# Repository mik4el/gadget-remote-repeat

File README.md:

# Remote repeat
Repeats IR remote signals received at e.g. a TV to a connected IR LED connected to a long wire placed e.g. inside a cabinet. This is also a minimal footprint platform to receive standard IR signals, manipulate them and to send standard IR signals.

## Hardware
The hardware consists of a standard IR receiver (TSOP38238) and an Attiny85 to process the signal and to control sending a new signal. The application is powered by USB micro from e.g. the USB output from a TV.

The pcb, where more details can be found in the hardware folder, is a minimal two layer pcb for the application. The top view of the current pcb can be viewed below:

## Software dependencies
The software is based on Arduino and uses the external library tiny_IRremote adopted by https://github.com/SeeJayDee from the popular https://github.com/z3t0/Arduino-IRremote library. I have made modifications to the library to be even smaller for the current usage. The modified library is in ```gadget-remote-repeat-tiny```. To include the current library please follow e.g. https://www.arduino.cc/en/Guide/Libraries to install an external library.

## Structure of repo
For an Attiny85 version of the software, please see ```gadget-remote-repeat-tiny```. For other Arduino platforms please see ```gadget-remote-repeat```.

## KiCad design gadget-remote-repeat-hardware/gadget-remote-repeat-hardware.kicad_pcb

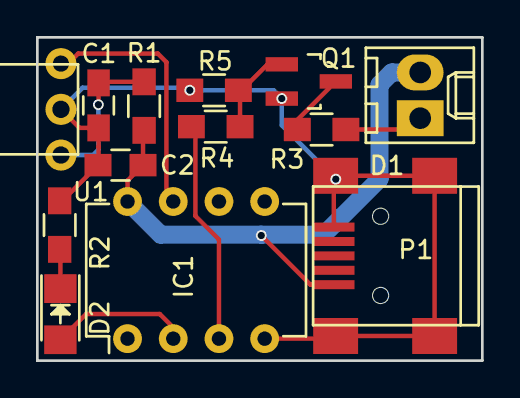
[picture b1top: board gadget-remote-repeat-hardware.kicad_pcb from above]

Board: 2 copper layers, 24.7 x 18.0 mm, 13 parts (0 on the bottom side), 10 nets.

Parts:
C1: 1uF; C_0805_HandSoldering
C2: 0.1uF; C_0805_HandSoldering
D1: IR-LED; Molex_KK-6410-02_02x2.54mm_Straight
D2: LED; LED_1206
IC1: ATTINY85-P; DIP-8_W7.62mm
P1: USB_OTG; USB_Mini-B
Q1: 2N7002; SOT-23_Handsoldering
R1: 500; R_0805_HandSoldering
R2: 2K; R_0805_HandSoldering
R3: 10; R_0805_HandSoldering
R4: 100; R_0805_HandSoldering
R5: 1K; R_0805_HandSoldering
U1: TSOP38238

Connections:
+5V: C2.1, D1.2, IC1.8, P1.1, R1.1
GND: C1.2, C2.2, IC1.4, P1.5, P1.6, Q1.2, R2.1, R5.2, U1.2
unnamed: C1.1, R1.2, U1.3
unnamed: D1.1, R3.2
unnamed: D2.1, R2.2
unnamed: D2.2, IC1.2
unnamed: IC1.3, R4.2
unnamed: IC1.7, U1.1
unnamed: Q1.1, R4.1, R5.1
unnamed: Q1.3, R3.1

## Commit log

2016-08-16 simple repeater to be verified
2016-08-16 sending power code works
2016-08-16 saving and storing raw signals tested
2016-08-17 functioning repeater tested
2016-08-17 tested attiny and went back to nano
2016-08-18 tested and works ok with attiny85
2016-08-21 made pcb and ordered v01
2016-09-09 adding pictures of finished hardware
